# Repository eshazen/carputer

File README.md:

# carputer

See [README-V1](README-V1.md) for version 1.

## V2.0 Hardware

Looking to design a "low profile" version with bare-metal software and comfortable RAM.
MCU candidate ATSAME51J20A.  (1M flash, 256k RAM).

**2026-11-14**

Bought a SAM E51 Curiosity Nano Evaluation Kit (EV76S68A).
Used Claude code to set up a blinky with all the required vendor headers, etc.
Created a new repo `https://github.com/eshazen/same51-car/` for now.

Planning to breakboard a setup with GPS and MicroSD card with this module.

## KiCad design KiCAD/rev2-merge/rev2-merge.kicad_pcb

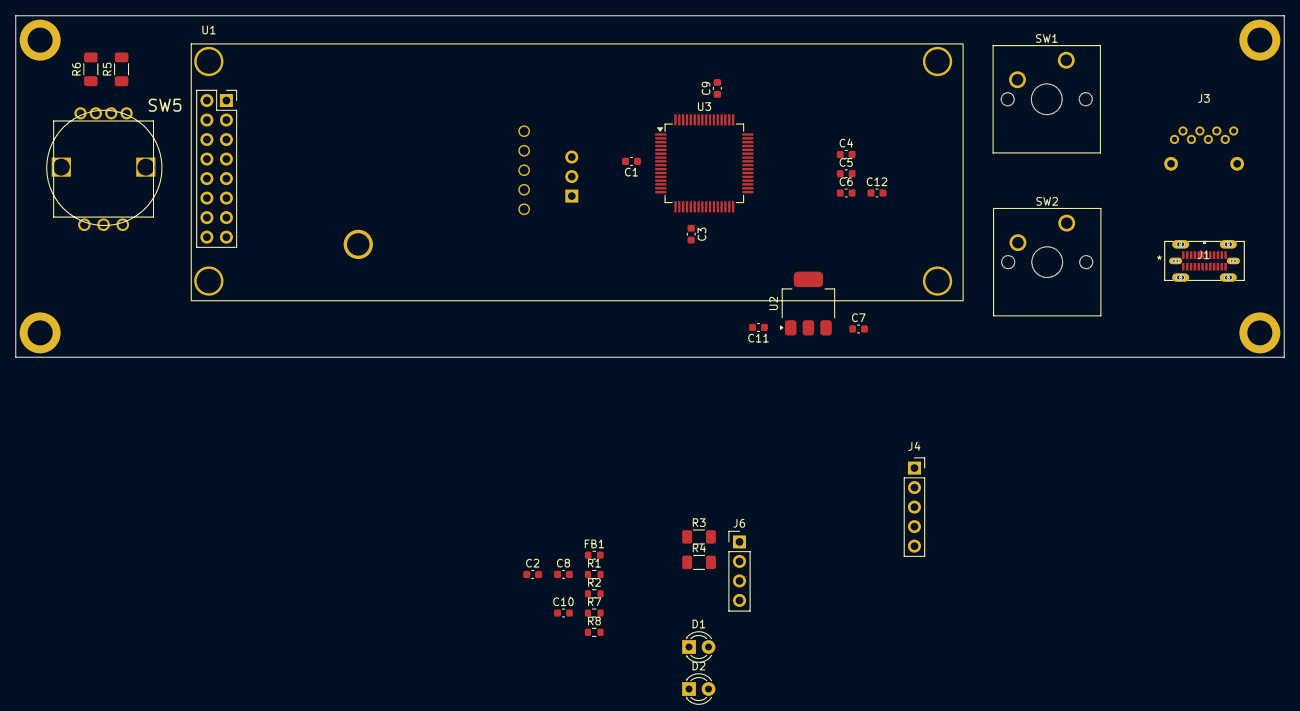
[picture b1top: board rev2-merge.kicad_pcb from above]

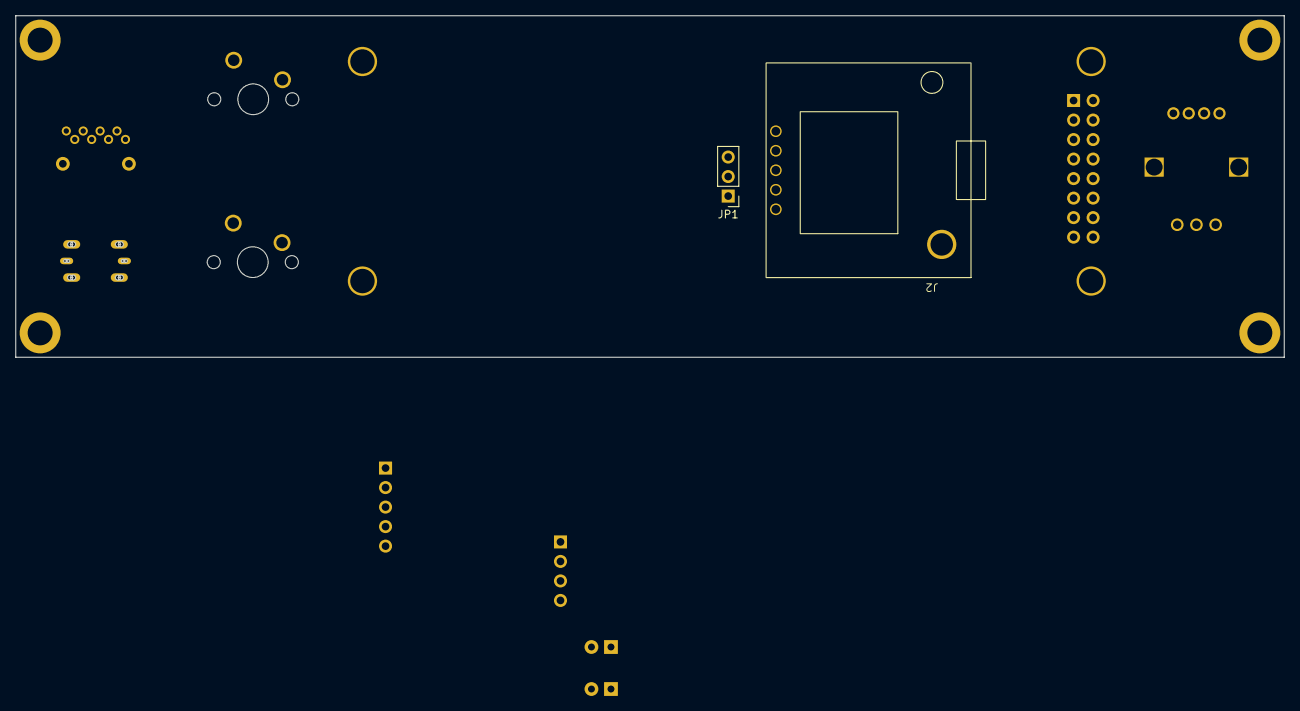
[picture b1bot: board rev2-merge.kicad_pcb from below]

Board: 2 copper layers, 165.1 x 44.5 mm, 39 parts (2 on the bottom side), 35 nets, no tracks yet.

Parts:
C1, C2, C3, C4, C5, C6, C12: 0.1uF; C_0603_1608Metric
C7, C8, C9, C10, C11: 10uF; C_0603_1608Metric
D1, D2: LED; LED_D3.0mm
FB1: FerriteBead_Small; L_0603_1608Metric
H1, H2, H3, H4: MountingHole; mtg_hole_4-40
J1: USB_C_Receptacle_USB2.0_14P; 204711-0001_MOL
J2: Conn_01x05; gps_module
J3: PJS008U-3000-0; microsd
J4: Conn_01x04; PinSocket_1x05_P2.54mm_Vertical
J6: Conn_01x04; PinHeader_1x04_P2.54mm_Vertical
JP1: Jumper_3_Bridged12; PinHeader_1x03_P2.54mm_Vertical
R1, R2: 4.7k; R_0603_1608Metric
R3, R4: 1k; R_1206_3216Metric_Pad1.30x1.75mm_HandSolder
R5, R6: 470; R_1206_3216Metric_Pad1.30x1.75mm_HandSolder
R7, R8: 5.1k; R_0603_1608Metric
SW1, SW2: SW_Push; SW_Cherry_MX_1.00u_PCB
SW5: COM-15140; rotary-RG-3D
U1: OLED-SSD1322; OLED_312_16pin
U2: AZ1117CH2-3.3; SOT-223-3_TabPin2
U3: ATSAME51J20A-A; TQFP-64_10x10mm_P0.5mm

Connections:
+3.3V: C4.1, C5.1, C6.1, C7.1, C12.1, FB1.2, J3.4 (VDD), J6.2, R1.1, R2.1, R3.1, R4.1, U1.2 (VCC), U2.3 (OUT), U3.34 (VDDIO), U3.48 (VDDIO), U3.56 (VDDIO)
+5V: J2.1, JP1.1 (A)
/CS0: J3.2 (CD/DAT3), U3.41 (PA20)
/DC: U1.14 (DC), U3.63 (PB02)
/ENC_A: SW5.A, U3.3 (PA02)
/ENC_B: SW5.B, U3.4 (PA03)
/ENC_GRN: R6.2, U3.62 (PB01)
/ENC_RED: R5.2, U3.61 (PB00)
/ENC_SW: SW5.4 (S1), U3.13 (PA04)
/LED0: D1.1 (K), U3.14 (PA05)
/LED1: D2.1 (K), U3.15 (PA06)
/MISO: J3.7 (DAT0), U3.38 (PA19)
/MOSI: J3.3 (CMD), U1.5 (D1/SDA), U3.39 (PB16)
/RX: J4.3, U3.20 (PA11)
/SCK: J3.5 (CLK), U1.4 (D0/SCK), U3.36 (PA17)
/SCL: J6.4, R2.2, U3.18 (PA09)
/SDA: J6.3, R1.2, U3.17 (PA08)
/TX: J4.4, U3.19 (PA10)
/USB-DM: J1.A7 (D-), J1.B7 (D-), U3.45 (PA24)
/USB-DP: J1.A6 (D+), J1.B6 (D+), U3.46 (PA25)
/~CS: U1.15 (~CS), U3.64 (PB03)
/~RST: U1.16 (~RST), U3.5 (PB04)
GND: C1.2, C2.2, C3.2, C4.2, C5.2, C6.2, C7.2, C8.2, C9.2, C10.2, C11.2, C12.2, J1.A1 (GND), J1.A12 (GND), J1.B1 (GND), J1.B12 (GND), J2.2, J3.6 (VSS), J3.MP1 (Mount), J3.MP2 (Mount), J4.2, J6.1, SW1.2, SW2.2, SW5.1 (S2), SW5.C, U1.1 (GND), U1.7 (D3), U1.8 (D4), U1.9 (D5), U1.10 (D6), U1.11 (D7), U1.12 (RD), U1.13 (WR), U3.7 (GNDANA), U3.22 (GND), U3.33 (GND), U3.47 (GND), U3.54 (GND)
unnamed: D1.2 (A), R3.2
unnamed: D2.2 (A), R4.2
unnamed: J1.A5 (CC1), R8.1
unnamed: J1.B5 (CC2), R7.1
unnamed: J4.1, JP1.2 (C)
unnamed: R6.1, SW5.3 (GREEN)
unnamed: R5.1, SW5.2 (RED)
unnamed: R7.2, R8.2, U2.2 (GND)
unnamed: C11.1, J1.A4 (VBUS), J1.A9 (VBUS), J1.B4 (VBUS), J1.B9 (VBUS), U2.1 (IN)
unnamed: C1.1, C10.1, FB1.1, U3.8 (VDDANA)
unnamed: C2.1, C9.1, U3.53 (VDDCORE)
unnamed: C3.1, C8.1, U3.21 (VDDIOB)

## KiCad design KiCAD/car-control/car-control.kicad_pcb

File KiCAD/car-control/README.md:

# ECOS for rev 1

* R3, R4 too small, LEDs way too bright!
  * Change to 3.3k
* Tx and Rx reversed? (works fine with 1:1 cable on SCOS board though)

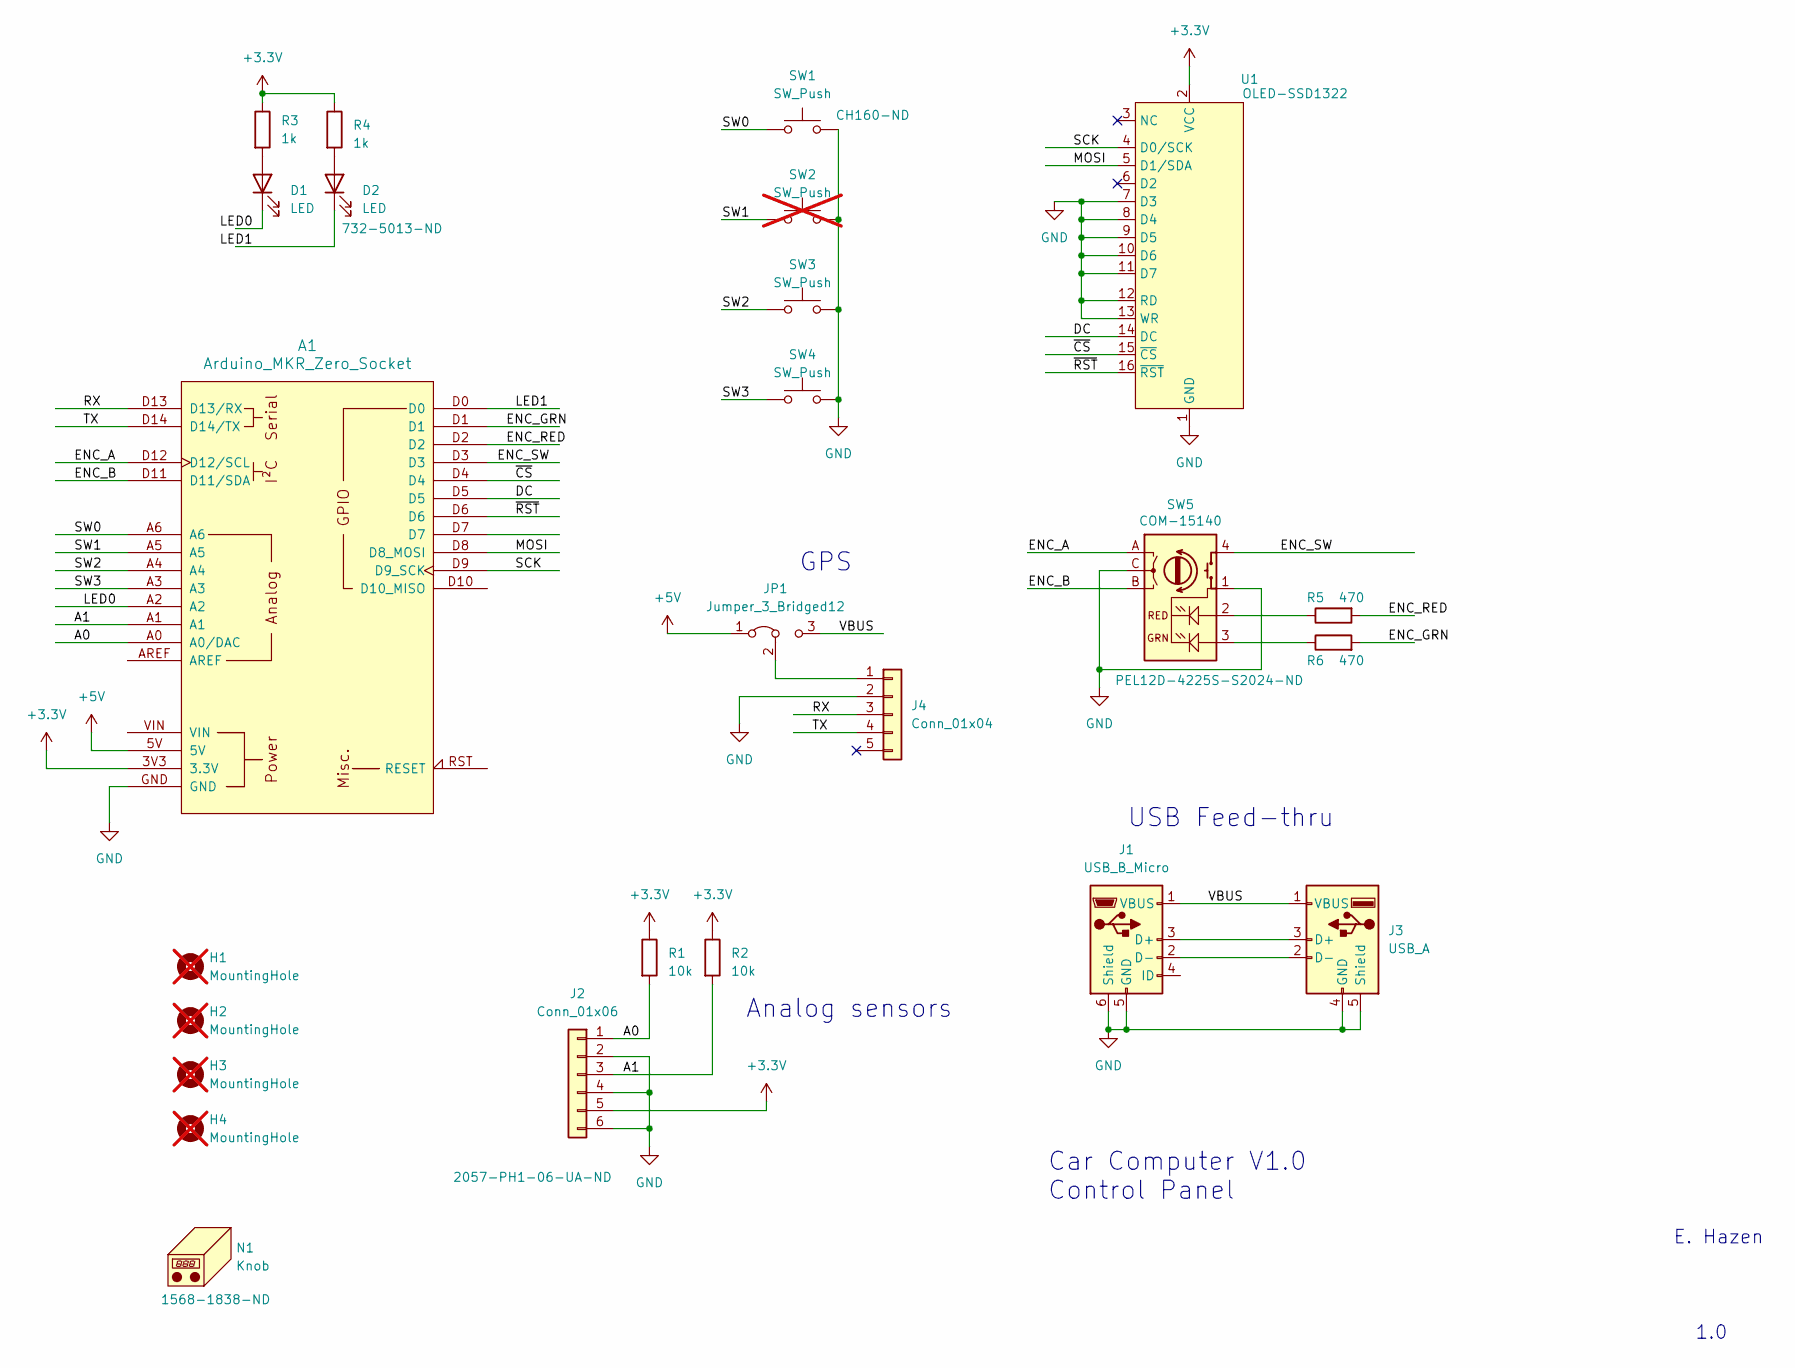
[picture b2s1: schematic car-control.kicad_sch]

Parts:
A1: Arduino_MKR_Zero_Socket
D1, D2: LED; LED_D3.0mm
H1, H2, H3, H4: MountingHole; mtg_hole_4-40; not fitted
J1: USB_B_Micro; CONN_USB3131-30-0230-A_GCT
J2: Conn_01x06; PinHeader_1x06_P2.54mm_Vertical
J3: USB_A; CONN_USB-A-S-VT_ADM
J4: Conn_01x04; PinSocket_1x05_P2.54mm_Vertical
JP1: Jumper_3_Bridged12; PinHeader_1x03_P2.54mm_Vertical
N1: Knob
R1, R2: 10k; R_1206_3216Metric_Pad1.30x1.75mm_HandSolder
R3, R4: 1k; R_1206_3216Metric_Pad1.30x1.75mm_HandSolder
R5, R6: 470; R_1206_3216Metric_Pad1.30x1.75mm_HandSolder
SW1, SW3, SW4: SW_Push; SW_Cherry_MX_1.00u_PCB
SW2: SW_Push; SW_Cherry_MX_1.00u_PCB; not fitted
SW5: COM-15140; rotary-RG-3D
U1: OLED-SSD1322; OLED_312_16pin

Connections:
+3.3V: A1.3V3 (3.3V), J2.5, R1.1, R2.1, R3.1, R4.1, U1.2 (VCC)
+5V: A1.5V, JP1.1 (A)
/A0: A1.A0 (A0/DAC), J2.1, R1.2
/A1: A1.A1, J2.3, R2.2
/DC: A1.D5, U1.14 (DC)
/ENC_A: A1.D12 (D12/SCL), SW5.A
/ENC_B: A1.D11 (D11/SDA), SW5.B
/ENC_GRN: A1.D1, R6.2
/ENC_RED: A1.D2, R5.2
/ENC_SW: A1.D3, SW5.4 (S1)
/LED0: A1.A2, D1.1 (K)
/LED1: A1.D0, D2.1 (K)
/MOSI: A1.D8 (D8_MOSI), U1.5 (D1/SDA)
/RX: A1.D13 (D13/RX), J4.3
/SCK: A1.D9 (D9_SCK), U1.4 (D0/SCK)
/SW0: A1.A6, SW1.1
/SW1: A1.A5, SW2.1
/SW2: A1.A4, SW3.1
/SW3: A1.A3, SW4.1
/TX: A1.D14 (D14/TX), J4.4
/VBUS: J1.1 (VBUS), J3.1 (VBUS), JP1.3 (B)
/~CS: A1.D4, U1.15 (~CS)
/~RST: A1.D6, U1.16 (~RST)
GND: A1.GND, J1.5 (GND), J1.6 (Shield), J2.2, J2.4, J2.6, J3.4 (GND), J3.5 (Shield), J4.2, SW1.2, SW2.2, SW3.2, SW4.2, SW5.1 (S2), SW5.C, U1.1 (GND), U1.7 (D3), U1.8 (D4), U1.9 (D5), U1.10 (D6), U1.11 (D7), U1.12 (RD), U1.13 (WR)
unnamed: D1.2 (A), R3.2
unnamed: D2.2 (A), R4.2
unnamed: J1.3 (D+), J3.3 (D+)
unnamed: J1.2 (D-), J3.2 (D-)
unnamed: J4.1, JP1.2 (C)
unnamed: R6.1, SW5.3 (GREEN)
unnamed: R5.1, SW5.2 (RED)

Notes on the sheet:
E. Hazen
GPS
USB Feed-thru
Car Computer V1.0 Control Panel
1.0
Analog sensors

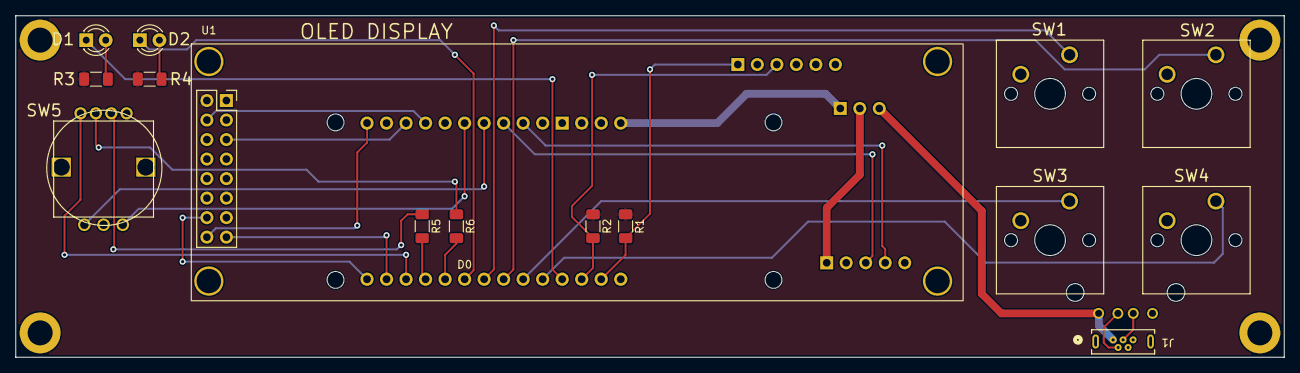
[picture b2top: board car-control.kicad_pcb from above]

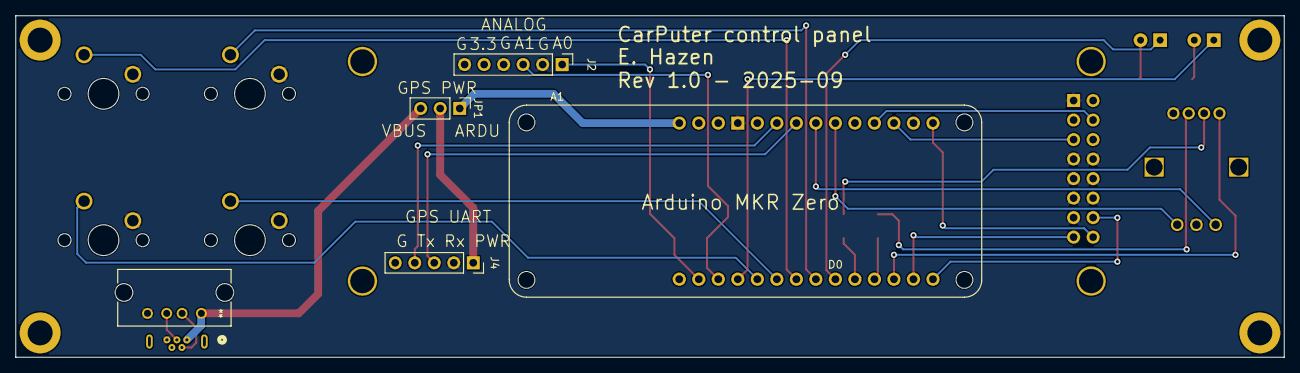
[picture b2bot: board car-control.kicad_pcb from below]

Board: 2 copper layers, 165.1 x 44.5 mm, 24 parts (5 on the bottom side), 31 nets.

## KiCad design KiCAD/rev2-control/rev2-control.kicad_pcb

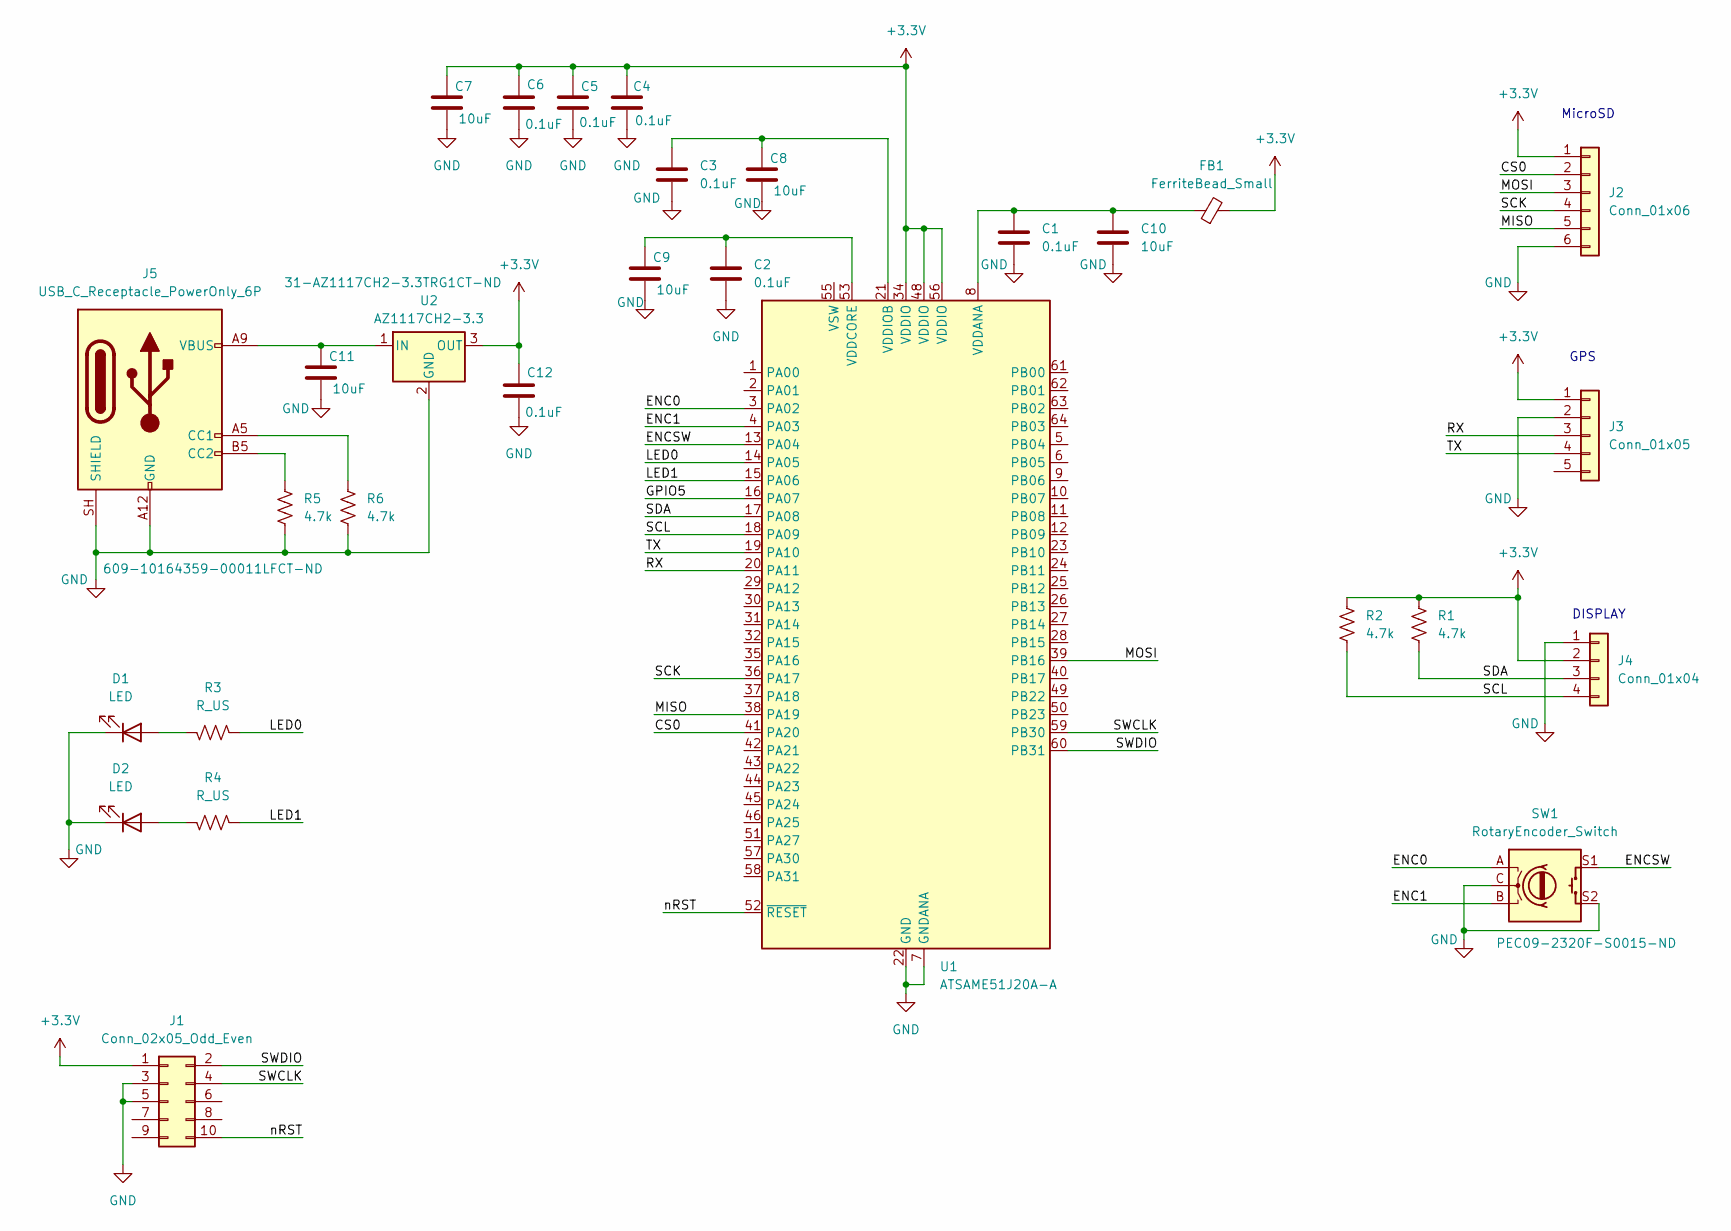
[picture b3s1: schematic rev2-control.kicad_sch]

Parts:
C1, C2, C3, C4, C5, C6, C12: 0.1uF; C_0603_1608Metric
C7, C8, C9, C10, C11: 10uF; C_0603_1608Metric
D1, D2: LED; LED_0603_1608Metric
FB1: FerriteBead_Small; L_0603_1608Metric
J1: Conn_02x05_Odd_Even; PinHeader_2x05_P2.54mm_Vertical
J2: Conn_01x06; PinHeader_1x06_P2.54mm_Vertical
J3: Conn_01x05; PinHeader_1x05_P2.54mm_Vertical
J4: Conn_01x04; PinHeader_1x04_P2.54mm_Vertical
J5: USB_C_Receptacle_PowerOnly_6P; AMPHENOL_10164359-00011LF; MPN 10164359-00011LF; DigiKey 609-10164359-00011LFCT-ND
R1, R2, R5, R6: 4.7k; R_0603_1608Metric
R3, R4: R_US; R_0603_1608Metric
SW1: RotaryEncoder_Switch; RotaryEncoder_Bourns_Horizontal_PEC09-2xxxF-Sxxxx; DigiKey PEC09-2320F-S0015-ND
U1: ATSAME51J20A-A; TQFP-64_10x10mm_P0.5mm
U2: AZ1117CH2-3.3; SOT-223-3_TabPin2; DigiKey 31-AZ1117CH2-3.3TRG1CT-ND

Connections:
+3.3V: C4.1, C5.1, C6.1, C7.1, C12.1, FB1.2, J1.1, J2.1, J3.1, J4.2, R1.1, R2.1, U1.34 (VDDIO), U1.48 (VDDIO), U1.56 (VDDIO), U2.3 (OUT)
/CS0: J2.2, U1.41 (PA20)
/ENC0: SW1.A, U1.3 (PA02)
/ENC1: SW1.B, U1.4 (PA03)
/ENCSW: SW1.S1, U1.13 (PA04)
/GPIO5: U1.16 (PA07)
/LED0: R3.1, U1.14 (PA05)
/LED1: R4.1, U1.15 (PA06)
/MISO: J2.5, U1.38 (PA19)
/MOSI: J2.3, U1.39 (PB16)
/RX: J3.3, U1.20 (PA11)
/SCK: J2.4, U1.36 (PA17)
/SCL: J4.4, R2.2, U1.18 (PA09)
/SDA: J4.3, R1.2, U1.17 (PA08)
/SWCLK: J1.4, U1.59 (PB30)
/SWDIO: J1.2, U1.60 (PB31)
/TX: J3.4, U1.19 (PA10)
/nRST: J1.10, U1.52 (~RESET)
GND: C1.2, C2.2, C3.2, C4.2, C5.2, C6.2, C7.2, C8.2, C9.2, C10.2, C11.2, C12.2, D1.1 (K), D2.1 (K), J1.3, J1.5, J2.6, J3.2, J4.1, J5.A12 (GND), J5.B12 (GND), J5.SH (SHIELD), R5.2, R6.2, SW1.C, SW1.S2, U1.7 (GNDANA), U1.22 (GND), U1.33 (GND), U1.47 (GND), U1.54 (GND), U2.2 (GND)
unnamed: D1.2 (A), R3.2
unnamed: D2.2 (A), R4.2
unnamed: J5.A5 (CC1), R6.1
unnamed: J5.B5 (CC2), R5.1
unnamed: C1.1, C10.1, FB1.1, U1.8 (VDDANA)
unnamed: C2.1, C9.1, U1.53 (VDDCORE)
unnamed: C3.1, C8.1, U1.21 (VDDIOB)
unnamed: C11.1, J5.A9 (VBUS), J5.B9 (VBUS), U2.1 (IN)

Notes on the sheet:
GPS
MicroSD
DISPLAY

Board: 2 copper layers, 29 parts (0 on the bottom side), 26 nets, no tracks yet.

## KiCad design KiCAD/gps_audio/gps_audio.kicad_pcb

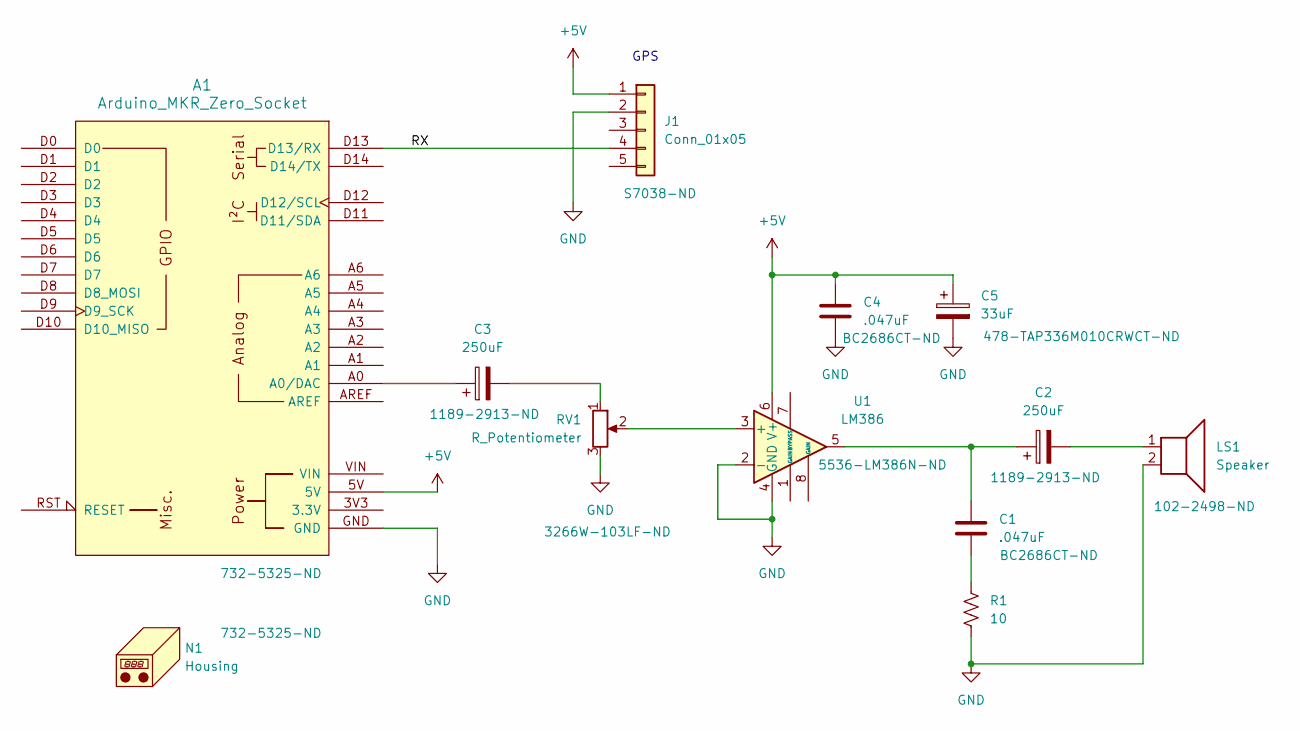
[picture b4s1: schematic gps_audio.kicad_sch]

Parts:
A1: Arduino_MKR_Zero_Socket
C1, C4: .047uF; C_Disc_D7.0mm_W2.5mm_P5.00mm
C2, C3: 250uF; CP_Radial_D6.3mm_P2.50mm
C5: 33uF; CP_Radial_Tantal_D4.5mm_P5.00mm
J1: Conn_01x05; gps_module
LS1: Speaker; CVS-1508_CUD
N1: Housing
R1: 10; R_Axial_DIN0207_L6.3mm_D2.5mm_P10.16mm_Horizontal
RV1: R_Potentiometer; Potentiometer_Bourns_3266W_Vertical
U1: LM386; DIP-8_W7.62mm

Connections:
+5V: A1.5V, C4.1, C5.1, J1.1, U1.6 (V+)
/RX: A1.D13 (D13/RX), J1.4
GND: A1.GND, C4.2, C5.2, J1.2, LS1.2, R1.2, RV1.3, U1.2 (-), U1.4 (GND)
unnamed: A1.A0 (A0/DAC), C3.1
unnamed: C1.1, C2.1, U1.5
unnamed: C1.2, R1.1
unnamed: C2.2, LS1.1
unnamed: C3.2, RV1.1
unnamed: RV1.2, U1.3 (+)

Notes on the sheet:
GPS

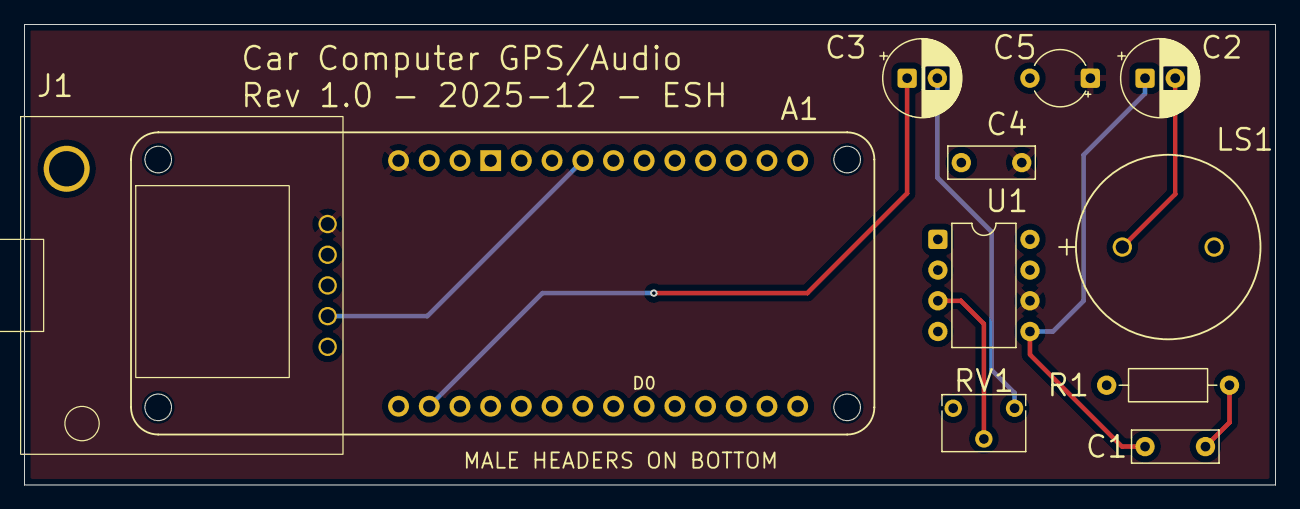
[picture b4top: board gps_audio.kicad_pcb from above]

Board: 2 copper layers, 103.5 x 38.1 mm, 11 parts (0 on the bottom side), 9 nets.

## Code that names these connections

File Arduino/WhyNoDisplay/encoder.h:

#ifndef ENCODER_H_INCLUDED
#define ENCODER_H_INCLUDED

#include <RotaryEncoder.h>

#define ENC_A 12
#define ENC_B 11
#define ENC_GRN 1
#define ENC_RED 2
#define ENC_SW 3

RotaryEncoder *encoder = nullptr;

void encoder_setup() {
  pinMode( ENC_A, INPUT_PULLUP);
  pinMode( ENC_B, INPUT_PULLUP);
  pinMode( ENC_SW, INPUT_PULLUP);
  pinMode( ENC_RED, OUTPUT);
  pinMode( ENC_GRN, OUTPUT);

  encoder = new RotaryEncoder( ENC_A, ENC_B, RotaryEncoder::LatchMode::FOUR3);
}


#endif

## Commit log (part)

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2025-09-10 create repo, upload some OPs models
2025-09-10 documentation
2025-09-14 working on case
2025-09-15 working on mount
2025-09-15 working on front panel model
2025-09-15 rename KiCAD project
2025-09-15 working on PCB
2025-09-15 working on layout
2025-09-16 working on layout, move USB
2025-09-20 PCB done?
2025-09-20 latest mount
2025-09-22 updates to case
2025-09-22 standoffs
2025-09-22 standoffs, final? gerbers
2025-09-23 case
2025-09-25 software
2025-09-26 initial software, fix layout
2025-09-26 GPS test display
2025-09-26 PCB V1.0 as built
2025-09-27 working on data extraction
2025-09-27 working on data
2025-09-29 working on grid
2025-09-29 save CSV files!
2025-09-29 adding back CSV files, working index?
2025-09-29 working on embedded code simulation
2025-09-29 debugging simulation
2025-09-30 working with qsort
2025-09-30 working on FindLocs.ino
2025-09-30 FindLocs.ino compiles!
2025-10-01 FindLocs serial working
2025-10-01 FindLocs not compiling
2025-10-01 Old FindLocs moved to FindLocsSerial, FindLocs compiles now
2025-10-02 works (is) but crashes after 3 updates
2025-10-05 seems to work, needs display work
2025-10-05 tweaking the display
2025-10-06 fix lip on front panel
2025-10-06 tweaking front panel
2025-10-08 tweaking the dimensions
2025-10-14 last enclosure tweaks
2025-10-14 update panel and box
2025-10-15 label.scad has text labels on front panel
2025-10-16 readme, diners
2025-10-19 working on V2 software
2025-10-23 ControlTest working with interrupts
2025-10-23 shaft encoder readout in FindLocs2
2025-10-23 working on groups
2025-10-23 need a separate grid for each location type
2025-11-08 readme
2025-11-09 shapefile stuff
2025-11-17 restore FindLocs2
2025-11-19 rtrees
2025-11-19 tweaks to shape
2025-11-19 working on r-trees
2025-11-20 working on file tree
2025-11-24 debugging with fake data
2025-11-24 work
2025-11-25 add search to grid_eval
2025-11-27 starting re-work for multi-part files
2025-11-30 about to re-work lat/lon storage
2025-12-01 maybe some bugs in new file format
2025-12-02 working on file format
2025-12-11 fix some bugs
2025-12-11 fixed bug, need to work on merge
2025-12-14 initial working? desktop version
2025-12-15 debugging the arduino
2025-12-15 initial arduino version working
2025-12-18 first working lookup/display in ShapeDisplay
2025-12-18 no serial option
2025-12-19 ShapeDisplay working with GPS
2025-12-19 Rev 1.0 shape display
2025-12-19 readme, notes
2025-12-20 Audio PCB, download TZ shapefile, update notes
2025-12-22 version 1.2
2025-12-23 Rev 1.3 - add Boston neighborhoods
2025-12-23 add some more databases
2025-12-24 WhyNoDisplay working with timer and oled
2025-12-25 starting rework
2025-12-28 working on brute force search for ios
2025-12-28 clean
2026-01-12 starting work on sound
2026-01-14 add some dims
2026-01-15 Add speaker holder proto
2026-01-18 V2.0 with sound as ShapeDisplay2
2026-01-24 Deploy version with sound
2026-04-17 working on MA towns
2026-04-18 Add MA towns
